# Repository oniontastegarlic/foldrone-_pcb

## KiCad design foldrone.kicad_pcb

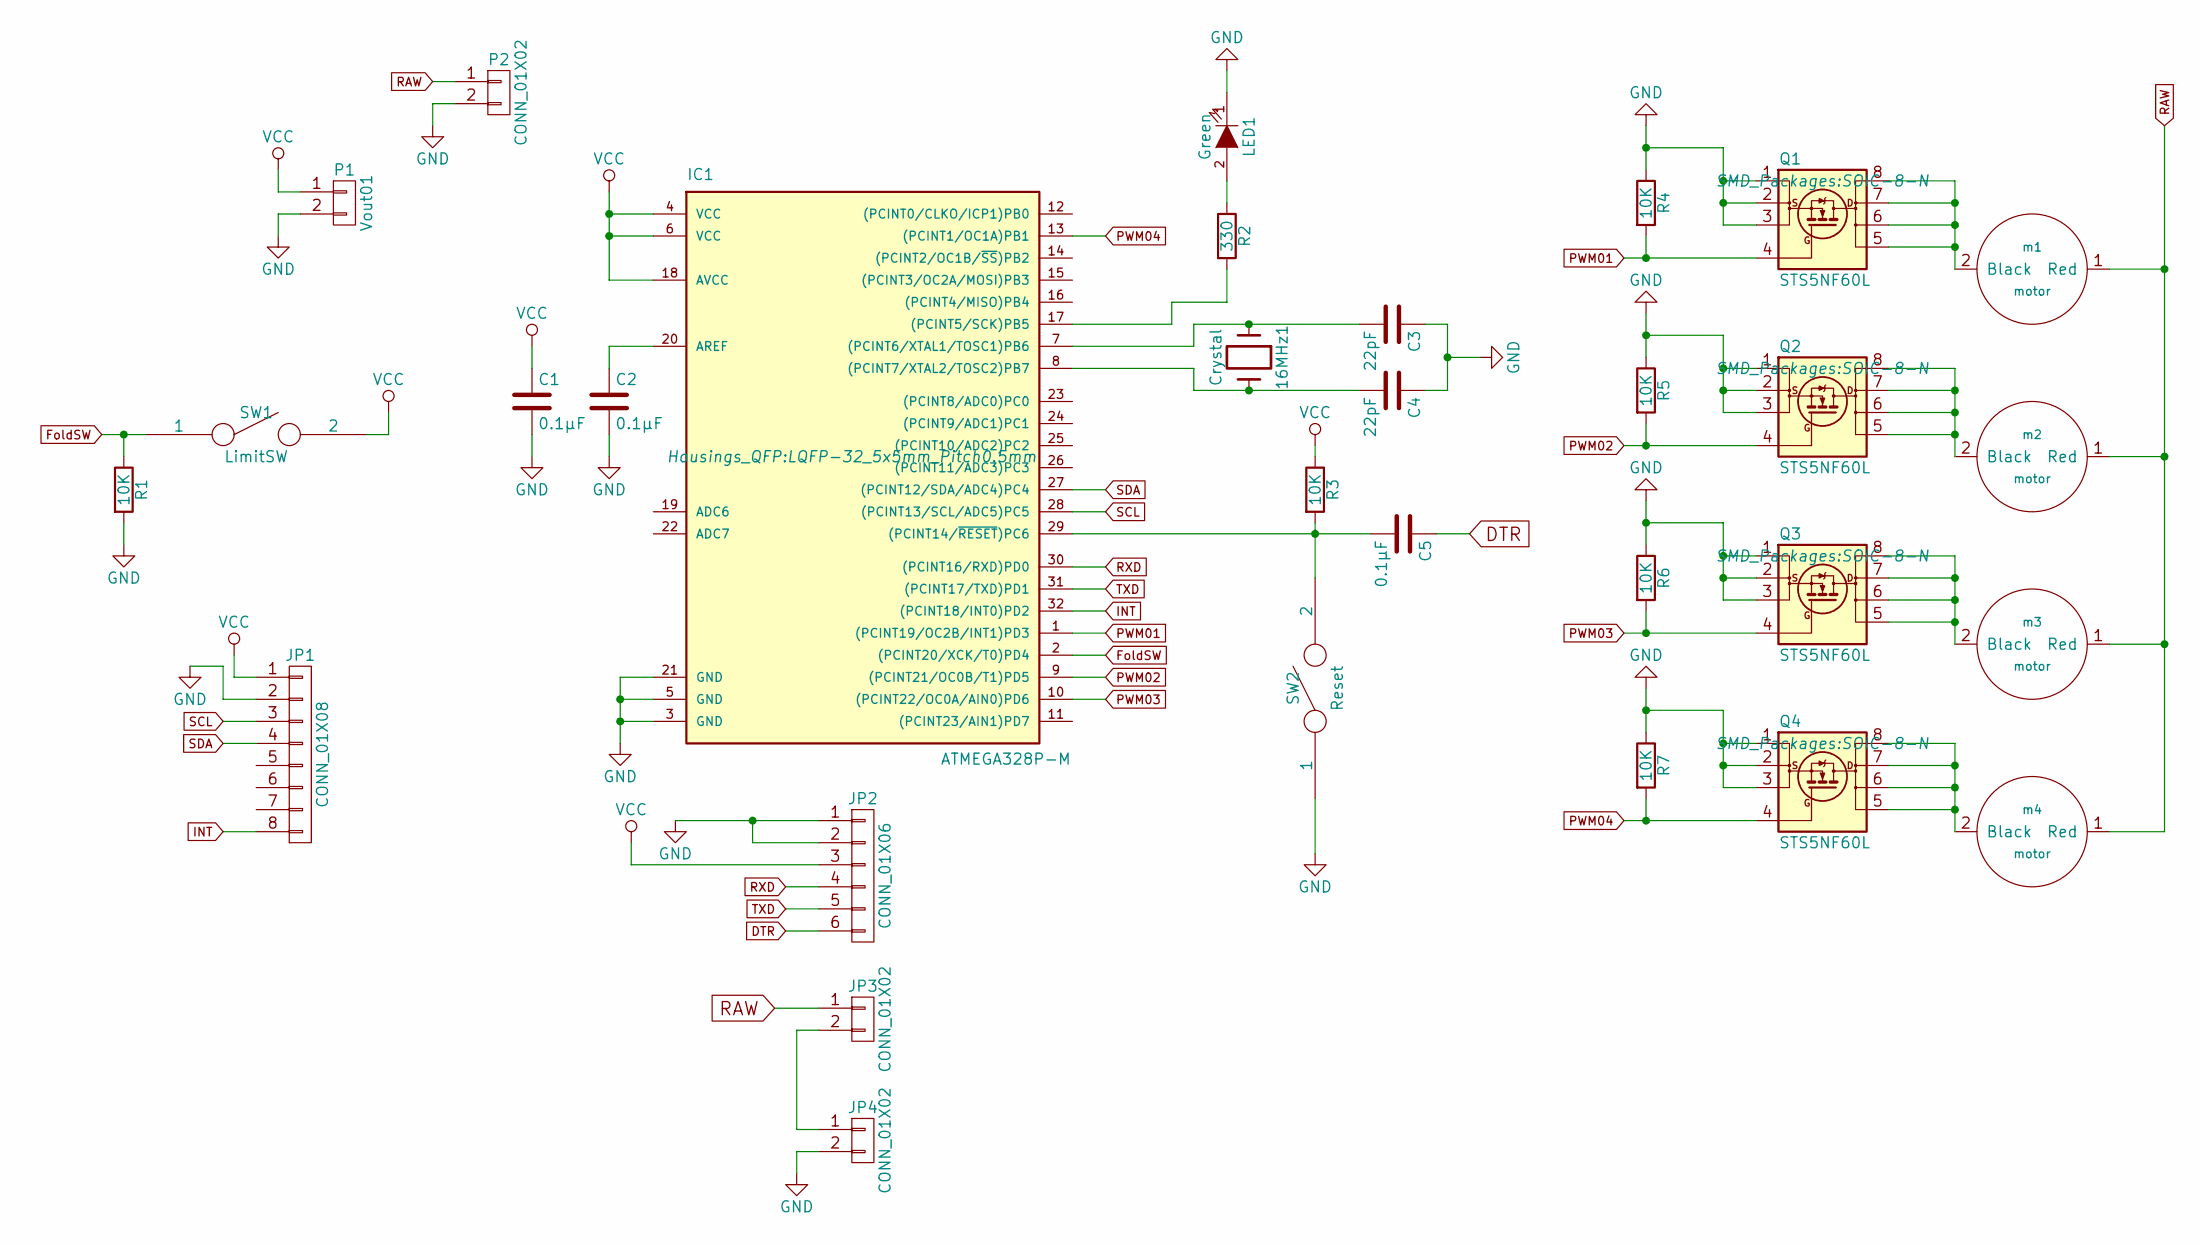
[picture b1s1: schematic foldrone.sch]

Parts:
16MHz1: Crystal; Crystal_HC49-U_Vertical
C1, C2, C5: 0.1μF; C_0603_HandSoldering
C3, C4: 22pF; C_0603_HandSoldering
IC1: ATMEGA328P-M; LQFP-32_5x5mm_Pitch0.5mm
JP1: CONN_01X08; Socket_Strip_Straight_1x08
JP2: CONN_01X06; Socket_Strip_Straight_1x06
JP3, JP4: CONN_01X02; Molex_PicoBlade_53047-0210
LED1: Green; LED_0603
P1: Vout01; Socket_Strip_Straight_1x02
P2: CONN_01X02; Socket_Strip_Straight_1x02
Q1, Q2, Q3, Q4: STS5NF60L; SOIC-8-N
R1, R3, R4, R5, R6, R7: 10K; R_0603_HandSoldering
R2: 330; R_0603_HandSoldering
SW1: LimitSW; Molex_PicoBlade_53047-0210
SW2: Reset; SW_SPST_FSMSM
m1, m2, m3, m4: motor; Socket_Strip_Straight_1x02

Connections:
DTR: C5.1, JP2.6
FoldSW: IC1.2 ((PCINT20/XCK/T0)PD4), R1.1, SW1.1
GND: C1.2, C2.2, C3.1, C4.1, IC1.3 (GND), IC1.5 (GND), IC1.21 (GND), JP1.2, JP2.1, JP2.2, JP4.2, LED1.1 (K), P1.2, P2.2, Q1.1 (S), Q1.2 (S), Q1.3 (S), Q2.1 (S), Q2.2 (S), Q2.3 (S), Q3.1 (S), Q3.2 (S), Q3.3 (S), Q4.1 (S), Q4.2 (S), Q4.3 (S), R1.2, R4.1, R5.1, R6.1, R7.1, SW2.1
INT: IC1.32 ((PCINT18/INT0)PD2), JP1.8
unnamed: 16MHz1.1, C3.2, IC1.7 ((PCINT6/XTAL1/TOSC1)PB6)
unnamed: 16MHz1.2, C4.2, IC1.8 ((PCINT7/XTAL2/TOSC2)PB7)
unnamed: C2.1, IC1.20 (AREF)
unnamed: C5.2, IC1.29 ((PCINT14/~RESET~)PC6), R3.2, SW2.2
unnamed: IC1.17 ((PCINT5/SCK)PB5), R2.2
unnamed: JP3.2, JP4.1
unnamed: LED1.2 (A), R2.1
unnamed: Q1.5 (D), Q1.6 (D), Q1.7 (D), Q1.8 (D), m1.2 (Black)
unnamed: Q2.5 (D), Q2.6 (D), Q2.7 (D), Q2.8 (D), m2.2 (Black)
unnamed: Q3.5 (D), Q3.6 (D), Q3.7 (D), Q3.8 (D), m3.2 (Black)
unnamed: Q4.5 (D), Q4.6 (D), Q4.7 (D), Q4.8 (D), m4.2 (Black)
PWM01: IC1.1 ((PCINT19/OC2B/INT1)PD3), Q1.4 (G), R4.2
PWM02: IC1.9 ((PCINT21/OC0B/T1)PD5), Q2.4 (G), R5.2
PWM03: IC1.10 ((PCINT22/OC0A/AIN0)PD6), Q3.4 (G), R6.2
PWM04: IC1.13 ((PCINT1/OC1A)PB1), Q4.4 (G), R7.2
RAW: JP3.1, P2.1, m1.1 (Red), m2.1 (Red), m3.1 (Red), m4.1 (Red)
RXD: IC1.30 ((PCINT16/RXD)PD0), JP2.4
SCL: IC1.28 ((PCINT13/SCL/ADC5)PC5), JP1.3
SDA: IC1.27 ((PCINT12/SDA/ADC4)PC4), JP1.4
TXD: IC1.31 ((PCINT17/TXD)PD1), JP2.5
VCC: C1.1, IC1.4 (VCC), IC1.6 (VCC), IC1.18 (AVCC), JP1.1, JP2.3, P1.1, R3.1, SW1.2

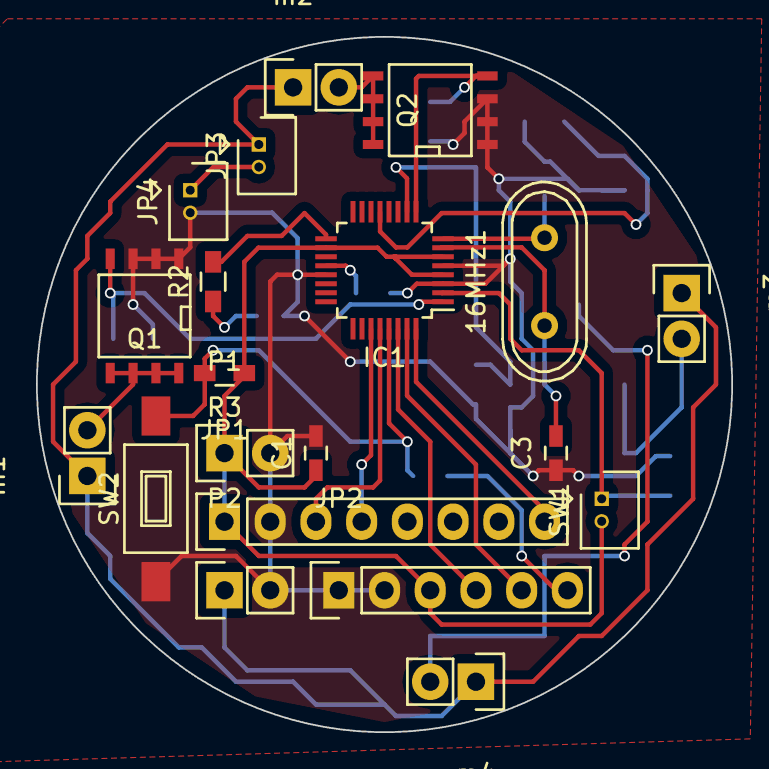
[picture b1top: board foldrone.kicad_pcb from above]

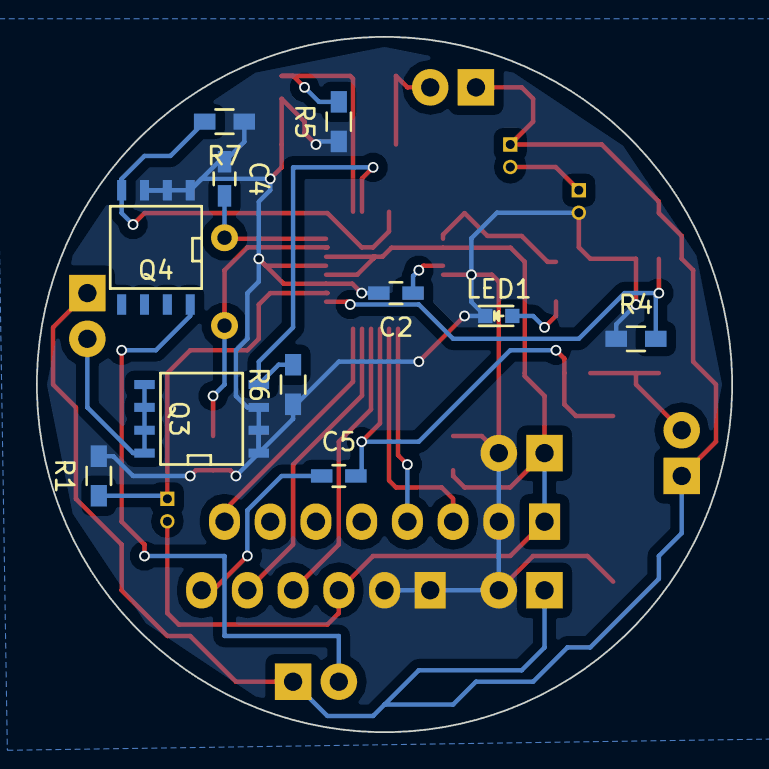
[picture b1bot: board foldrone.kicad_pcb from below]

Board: 2 copper layers, 38.6 x 38.6 mm, 31 parts (11 on the bottom side), 25 nets.

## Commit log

2016-08-26 First pcb
2016-08-29 Proto PCB ready
